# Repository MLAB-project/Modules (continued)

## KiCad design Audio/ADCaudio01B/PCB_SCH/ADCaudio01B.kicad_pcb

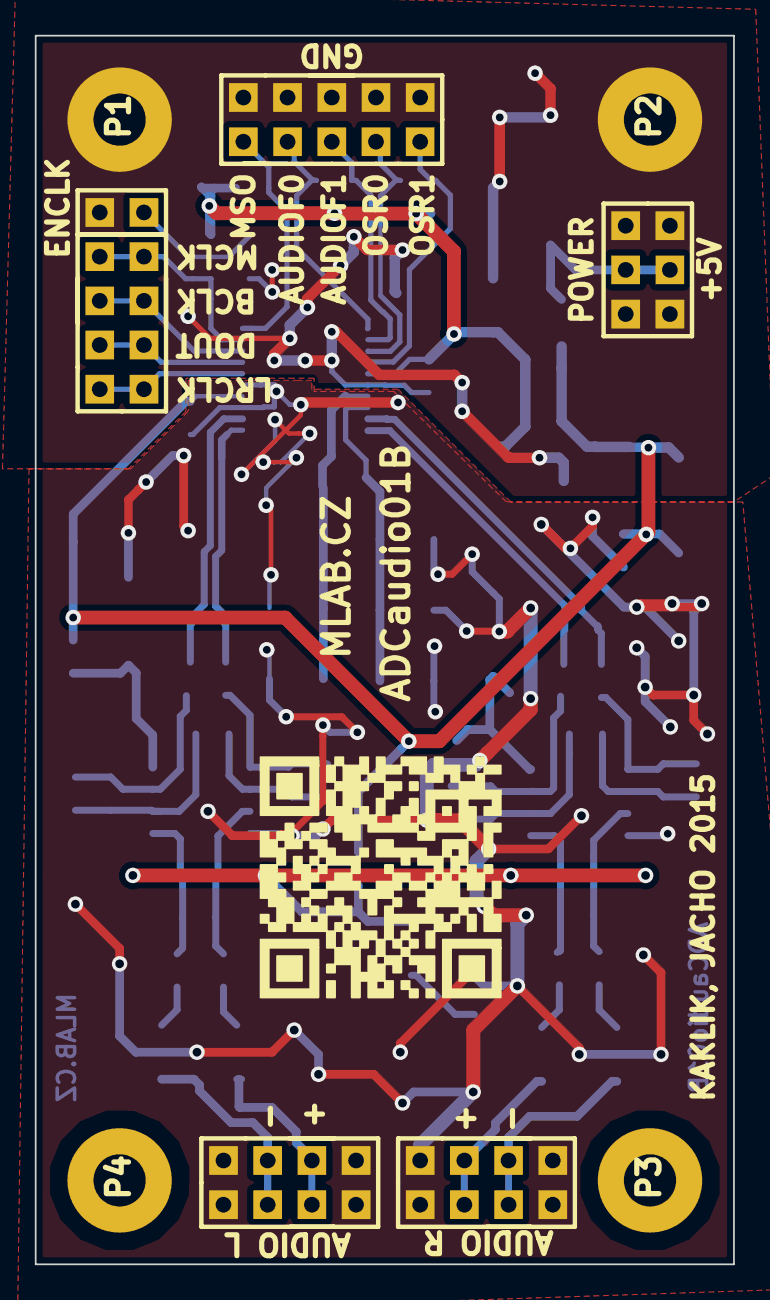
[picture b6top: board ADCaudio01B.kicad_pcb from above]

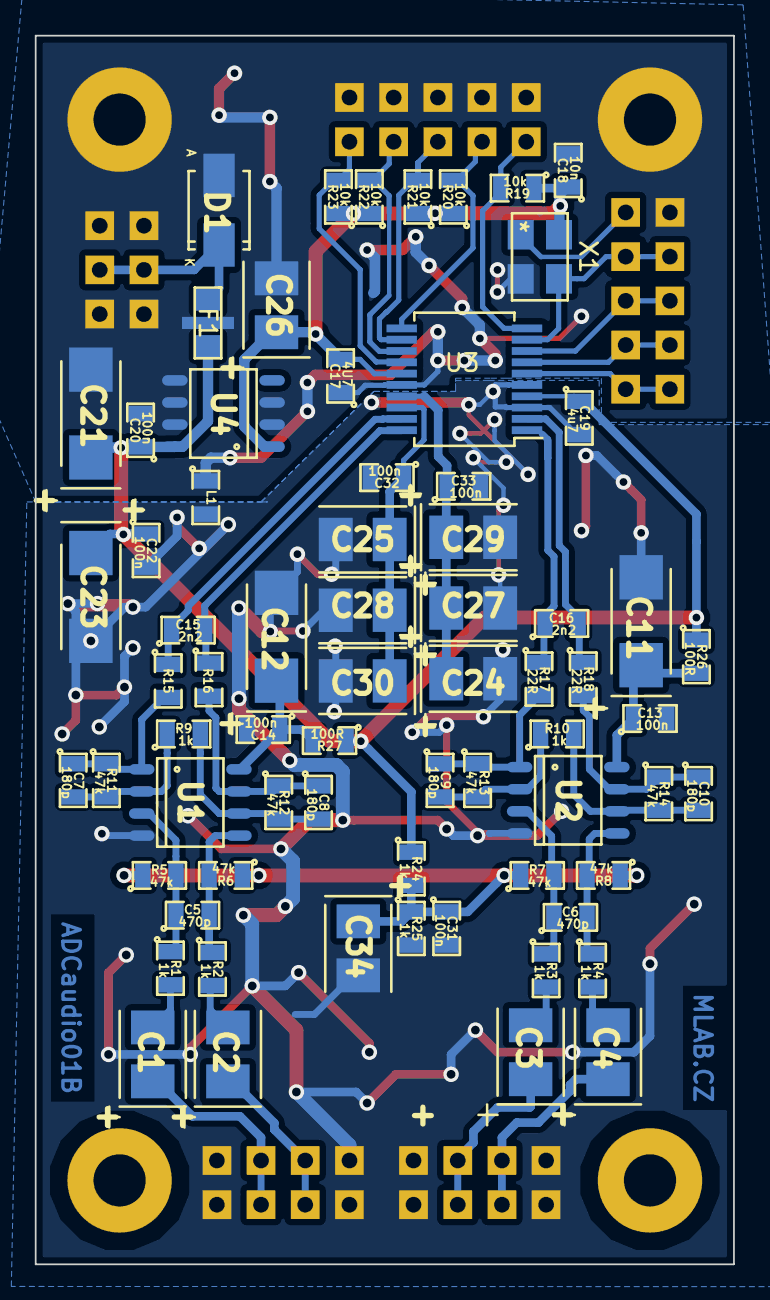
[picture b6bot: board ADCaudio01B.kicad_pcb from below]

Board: 2 copper layers, 40.1 x 70.6 mm, 79 parts (69 on the bottom side), 44 nets.

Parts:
C1, C2, C3, C4, C24, C25, C26, C27, C28, C29, C30: 10u; TantalC_SizeB_Reflow
C5, C6: 470p; SMD-0805
C7, C8, C9, C10: 180p; SMD-0805
C11, C12, C21, C23: 47u; TantalC_SizeC_Reflow
C13, C14, C20, C22, C31, C32, C33: 100n; SMD-0805
C15, C16: 2n2; SMD-0805
C17: 4U7; SMD-0805
C18: 10n; SMD-0805
C19: 4u7; SMD-0805
C34: 10uF; TantalC_SizeB_Reflow
D1: M4; Diode-SMA_Standard
F1: NFM21PC105; FIR1
J1, J2, J5: JUMP_4X2; Pin_Header_Straight_2x04
J3: JUMP_3X2; Pin_Header_Straight_2x03
J4: CONN1_2; Pin_Header_Straight_2x01
J6: JUMP2_5X2; Pin_Header_Straight_2x05
L1: BLM21PG300SN1D; SMD-0805
P1, P2, P3, P4: _; MountingHole_3mm
R1, R2, R3, R4, R9, R10, R24, R25: 1k; SMD-0805
R5, R6, R7, R8, R11, R12, R13, R14: 47k; SMD-0805
R15, R16, R17, R18: 22R; SMD-0805
R19, R20, R21, R22, R23: 10k; SMD-0805
R26, R27: 100R; SMD-0805
U1, U2: LT6231CS; SO-8
U3: WM8786; SSOP-20_5.3x7.2mm_Pitch0.65mm
U4: LE33CD; SO-8
X1: ASFL1-24.576MHZ-EK; ASFL1

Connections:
+3.3V: C17.2, C18.1, C26.1, R19.1, R20.1, R21.1, R22.1, R23.1, U3.15, U4.1, X1.4
+5V: C19.1, C20.1, C21.1, C22.1, C23.1, F1.3, R24.1, R26.1, R27.1, U3.4, U4.8
/AINL+: C16.1, R17.1, U3.1
/AINL-: C16.2, R18.1, U3.2
/AINR+: C15.2, R16.1, U3.20
/AINR-: C15.1, R15.1, U3.19
/AUDIOF0: J6.7, R20.2, U3.11
/AUDIOF1: J6.8, R21.2, U3.12
/AVDD/2: C31.1, C34.1, R5.1, R6.1, R7.1, R8.1, R24.2, R25.1
/BCLK: J5.3, J5.6, U3.8
/DOUT: J5.2, J5.7, U3.7
/LRCLK: J5.1, J5.8, U3.6
/MCLK: J5.4, J5.5, U3.9, X1.3
/MSO: J6.6, R19.2, U3.10
/OSR0: J6.9, R22.2, U3.13
/OSR1: J6.10, R23.2, U3.14
/VCC: C12.1, C14.1, R27.2, U1.8
/VCC1: C11.1, C13.1, R26.2, U2.8
/VMIO: C24.1, C27.1, C29.1, C33.1, U3.17
/VREF: C25.1, C28.1, C30.1, C32.1, U3.18
DGND: C17.1, C18.2, C20.2, C21.2, C26.2, D1.1, F1.2, J3.1, J3.3, J3.4, J3.6, J4.1, J6.1, J6.2, J6.3, J6.4, J6.5, L1.1, P1.1, P2.1, U3.16, U4.2, U4.3, U4.5, U4.6, U4.7, X1.2
GNDA: C11.2, C12.2, C13.2, C14.2, C19.2, C22.2, C23.2, C24.2, C25.2, C27.2, C28.2, C29.2, C30.2, C31.2, C32.2, C33.2, C34.2, J1.1, J1.4, J1.5, J1.8, J2.1, J2.4, J2.5, J2.8, L1.2, R25.2, U1.4, U2.4, U3.3, U3.5
unnamed: C1.1, J1.3, J1.6
unnamed: C1.2, R1.2
unnamed: C2.1, J1.2, J1.7
unnamed: C2.2, R2.2
unnamed: C3.1, J2.3, J2.6
unnamed: C3.2, R3.2
unnamed: C4.1, J2.2, J2.7
unnamed: C4.2, R4.2
unnamed: C5.1, R1.1, R5.2, U1.3
unnamed: C5.2, R2.1, R6.2, U1.5
unnamed: C6.1, R3.1, R7.2, U2.3
unnamed: C6.2, R4.1, R8.2, U2.5
unnamed: C7.1, R11.1, R15.2, U1.1
unnamed: C7.2, R9.1, R11.2, U1.2
unnamed: C8.1, R12.1, R16.2, U1.7
unnamed: C8.2, R9.2, R12.2, U1.6
unnamed: C9.1, R13.1, R17.2, U2.1
unnamed: C9.2, R10.1, R13.2, U2.2
unnamed: C10.1, R14.1, R18.2, U2.7
unnamed: C10.2, R10.2, R14.2, U2.6
unnamed: D1.2, F1.1, J3.2, J3.5
unnamed: J4.2, X1.1

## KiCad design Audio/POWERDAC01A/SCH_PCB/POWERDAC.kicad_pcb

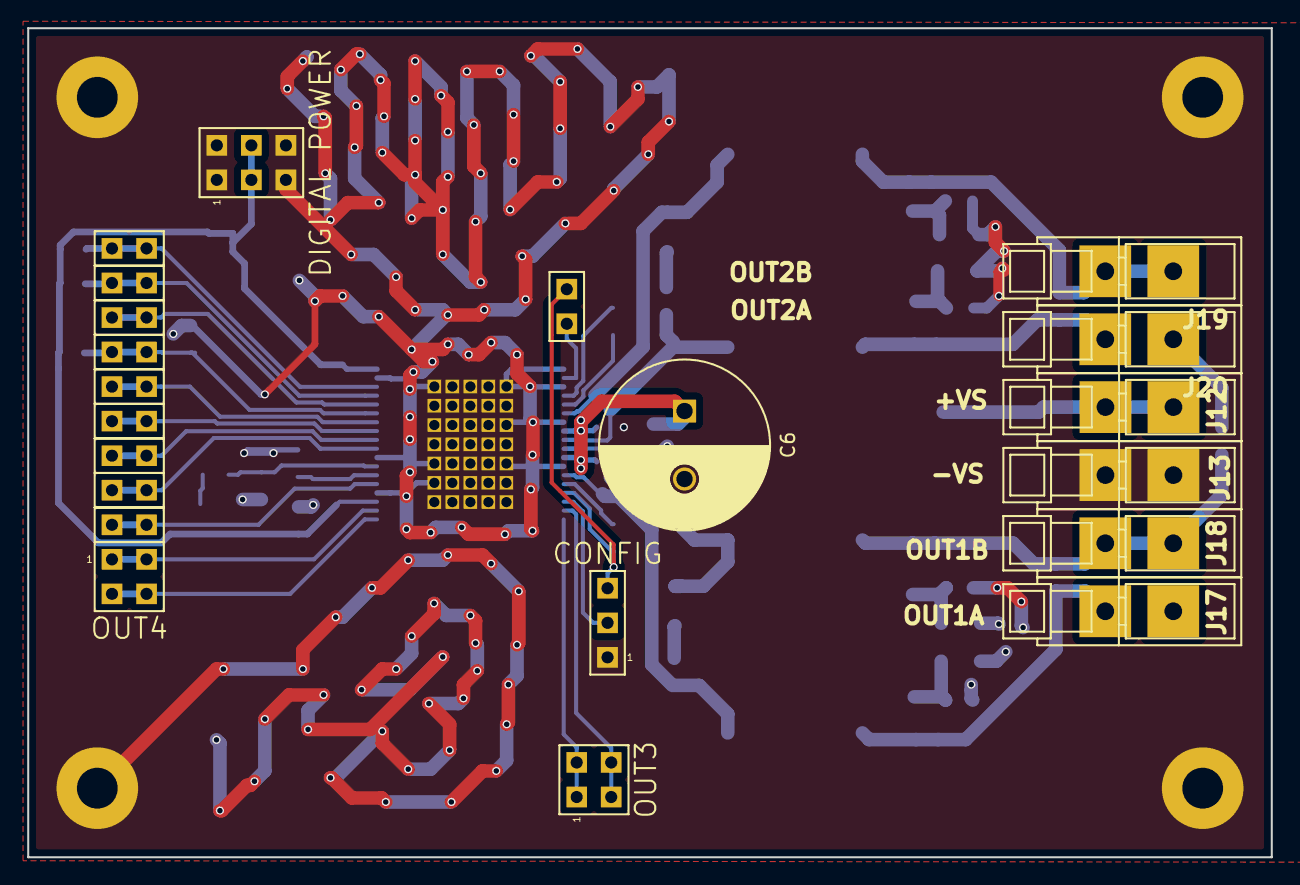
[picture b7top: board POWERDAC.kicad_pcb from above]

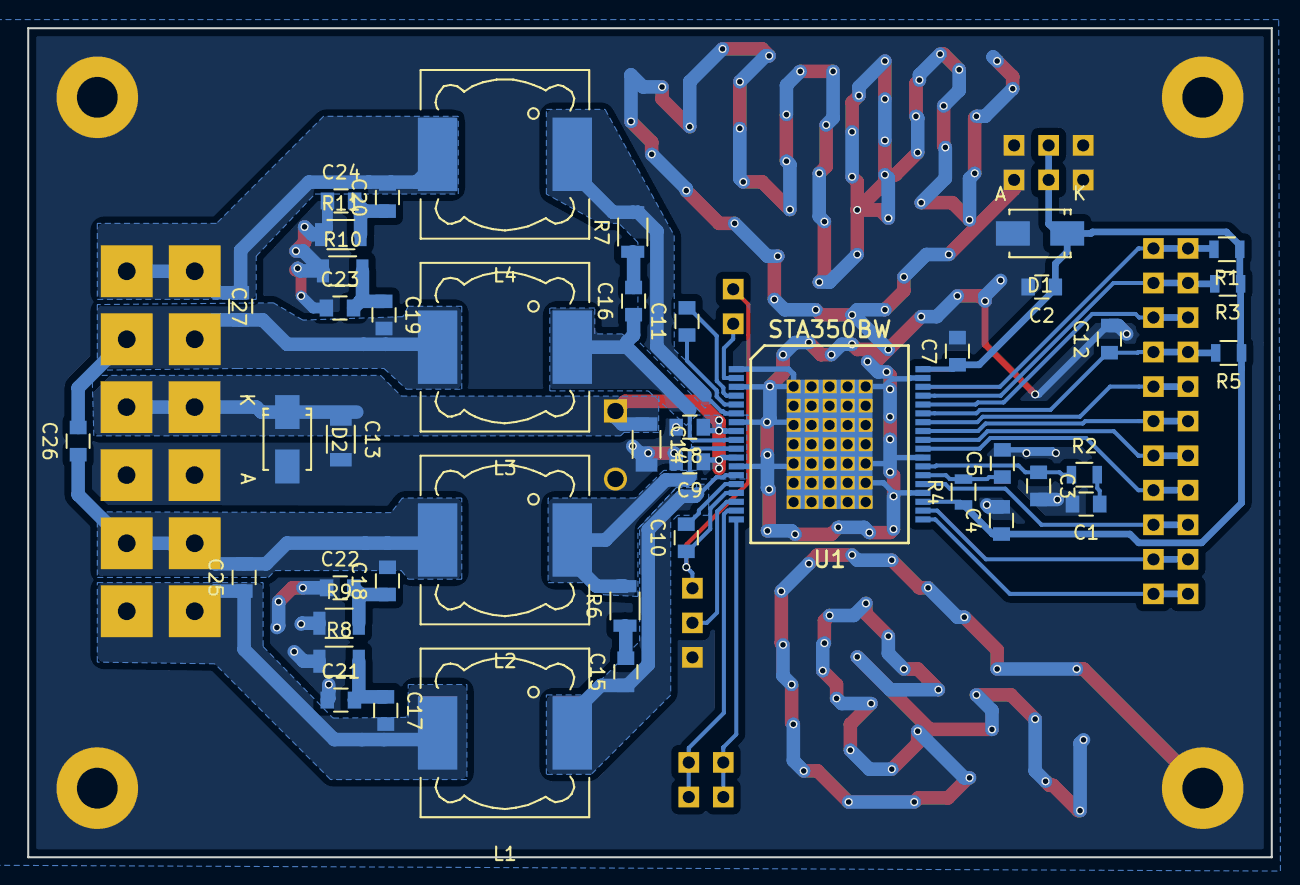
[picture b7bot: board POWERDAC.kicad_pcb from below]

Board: 2 copper layers, 91.4 x 61.0 mm, 69 parts (44 on the bottom side), 39 nets.

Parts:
C1: 4n7; C_0805
C2: 22uF/6.3V; C_0805
C3: 680p; C_0805
C4, C5, C7, C8, C9, C10, C11, C17, C18, C19, C20, C21, C22, C23, C24: 100nF; C_0805
C6: 1000uF/35V; C_Radial_D12.5_L25_P5
C12: 1nF; C_0805
C13, C14: 1uF/35V; C_1206
C15, C16: 330p; C_0805
C25, C27: 680nF; C_0805
C26: 1uF; C_0805
D1, D2: M4; SMA_Standard
J1: CONFIG; Straight_1x03
J2: DIGITAL POWER; Straight_2x03
J3: PWRDN; Straight_1x02
J4: INT_LINE; Straight_1x02
J5: SDA; Straight_1x02
J6: SCL; Straight_1x02
J7: SDI; Straight_1x02
J8: LRCKI; Straight_1x02
J9: XTI; Straight_1x02
J10: BICKI; Straight_1x02
J11: SA; Straight_1x02
J12: +VS; TerminalBlock_WAGO_256_RM5mm_1pol
J13: -VS; TerminalBlock_WAGO_256_RM5mm_1pol
J14: RESET; Straight_1x02
J15: OUT3; Straight_2x02
J16: OUT4; Straight_2x02
J17: OUT1A; TerminalBlock_WAGO_256_RM5mm_1pol
J18: OUT1B; TerminalBlock_WAGO_256_RM5mm_1pol
J19: OUT2B; TerminalBlock_WAGO_256_RM5mm_1pol
J20: OUT2A; TerminalBlock_WAGO_256_RM5mm_1pol
L1, L2, L3, L4: 15uH; Choke_SMD_12x12mm_h6mm
M1, M2, M3, M4: HOLE; MountingHole_3mm
R1, R3, R5: 10k; R_0805
R2: 2k2; R_0805
R4: 2R2; R_0805
R6, R7: 20; R_1206
R8, R9, R10, R11: 4R7; R_1206
U1: STA350BW; PowerSSO-36

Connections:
+3V3: C2.1, C4.1, C7.1, D1.1, J2.3, J2.4, R1.1, R3.1, R4.1, R5.1, U1.21, U1.36
GND: C1.2, C2.2, C3.2, C4.2, C5.2, C6.2, C7.2, C8.2, C9.2, C12.2, C13.2, C14.2, C21.1, C22.1, C23.1, C24.1, D1.2, D2.2, J1.1, J2.1, J2.2, J2.5, J2.6, J13.1, M1.1, M2.1, M3.1, M4.1, R8.1, R9.1, R10.1, R11.1, U1.1, U1.3, U1.7, U1.12, U1.22, U1.26, U1.35, U1.37
unnamed: C1.1, R2.2
unnamed: C3.1, R2.1, U1.25
unnamed: C5.1, R4.2, U1.24
unnamed: C10.2, U1.14
unnamed: C11.1, U1.5
unnamed: C11.2, U1.4
unnamed: C12.1, J14.1, J14.2, R5.2, U1.31
unnamed: C15.1, L1.1, U1.13
unnamed: C15.2, R6.1
unnamed: C16.1, L3.1, U1.9
unnamed: C16.2, R7.1
unnamed: C17.1, C21.2, R8.2
unnamed: C17.2, C25.1, J17.1, L1.2
unnamed: C18.1, C22.2, R9.2
unnamed: C18.2, C25.2, C26.1, J18.1, L2.2
unnamed: C19.1, C23.2, R10.2
unnamed: C19.2, C26.2, C27.1, J20.1, L3.2
unnamed: C20.1, C24.2, R11.2
unnamed: C20.2, C27.2, J19.1, L4.2
unnamed: J1.2, U1.16
unnamed: J3.1, J3.2, U1.23
unnamed: J4.1, J4.2, U1.32
unnamed: J5.1, J5.2, R3.2, U1.33
unnamed: J6.1, J6.2, R1.2, U1.34
unnamed: J7.1, J7.2, U1.30
unnamed: J8.1, J8.2, U1.29
unnamed: J9.1, J9.2, U1.27
unnamed: J10.1, J10.2, U1.28
unnamed: J11.2, U1.2
unnamed: J15.1, J15.2, U1.18
unnamed: J15.3, J15.4, U1.17
unnamed: J16.1, J16.2, U1.20
unnamed: J16.3, J16.4, U1.19
unnamed: L2.1, R6.2, U1.10
unnamed: L4.1, R7.2, U1.6
VCC: C6.1, C8.1, C9.1, C13.1, C14.1, D2.1, J12.1, U1.8, U1.11
VDD: C10.1, J1.3, J11.1, U1.15

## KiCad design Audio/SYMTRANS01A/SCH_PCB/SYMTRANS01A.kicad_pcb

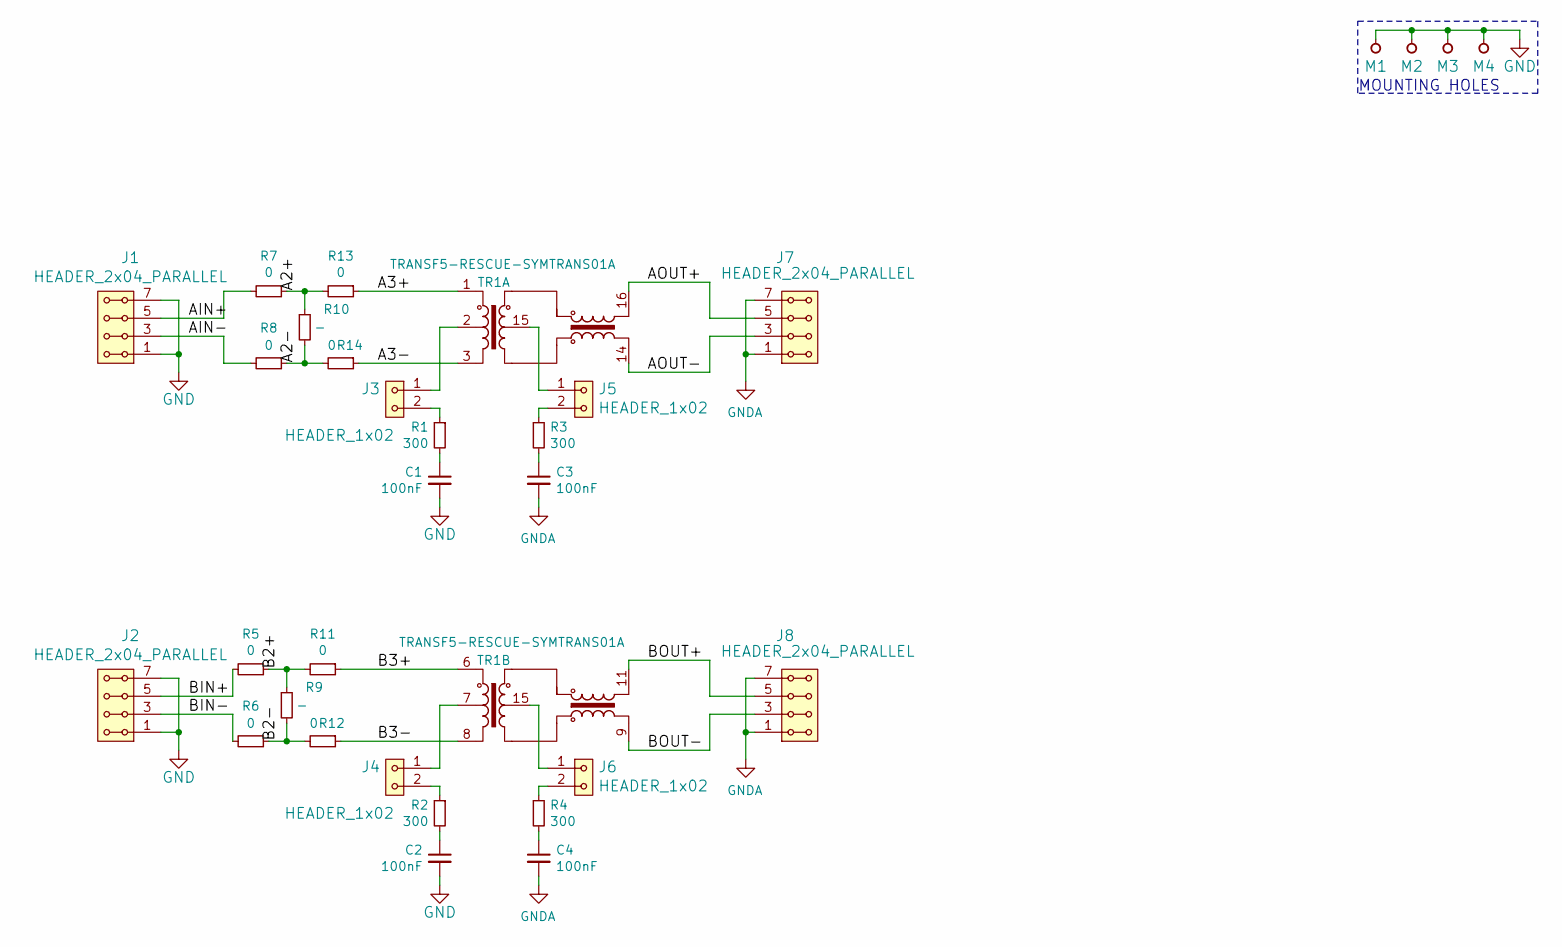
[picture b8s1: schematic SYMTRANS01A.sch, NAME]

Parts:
C1, C2, C3, C4: 100nF; SMD-0805
J1, J2, J7, J8: HEADER_2x04_PARALLEL; Straight_2x04
J3, J4, J5, J6: HEADER_1x02; Straight_2x01
M1, M2, M3, M4: HOLE; MountingHole_3mm
R1, R2, R3, R4: 300; SMD-0805
R5, R6, R7, R8, R11, R12, R13, R14: 0; SMD-0805
R9, R10: -; SMD-0805
TR1: TRANSF5-RESCUE-SYMTRANS01A; H110X_H1121_HX1188

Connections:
/A2+: R7.1, R10.1, R13.2
/A2-: R8.1, R10.2, R14.2
/A3+: R13.1, TR1.1
/A3-: R14.1, TR1.3
/AIN+: J1.5, J1.6, R7.2
/AIN-: J1.3, J1.4, R8.2
/AOUT+: J7.5, J7.6, TR1.16
/AOUT-: J7.3, J7.4, TR1.14
/B2+: R5.1, R9.1, R11.2
/B2-: R6.1, R9.2, R12.2
/B3+: R11.1, TR1.6
/B3-: R12.1, TR1.8
/BIN+: J2.5, J2.6, R5.2
/BIN-: J2.3, J2.4, R6.2
/BOUT+: J8.5, J8.6, TR1.11
/BOUT-: J8.3, J8.4, TR1.9
GND: C1.2, C2.2, J1.1, J1.2, J1.7, J1.8, J2.1, J2.2, J2.7, J2.8, M1.1, M2.1, M3.1, M4.1
GNDA: C3.2, C4.2, J7.1, J7.2, J7.7, J7.8, J8.1, J8.2, J8.7, J8.8
unnamed: C1.1, R1.2
unnamed: C2.1, R2.2
unnamed: C3.1, R3.2
unnamed: C4.1, R4.2
unnamed: J3.1, TR1.2
unnamed: J3.2, R1.1
unnamed: J4.1, TR1.7
unnamed: J4.2, R2.1
unnamed: J5.2, R3.1
unnamed: J6.2, R4.1

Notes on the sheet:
MOUNTING HOLES

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
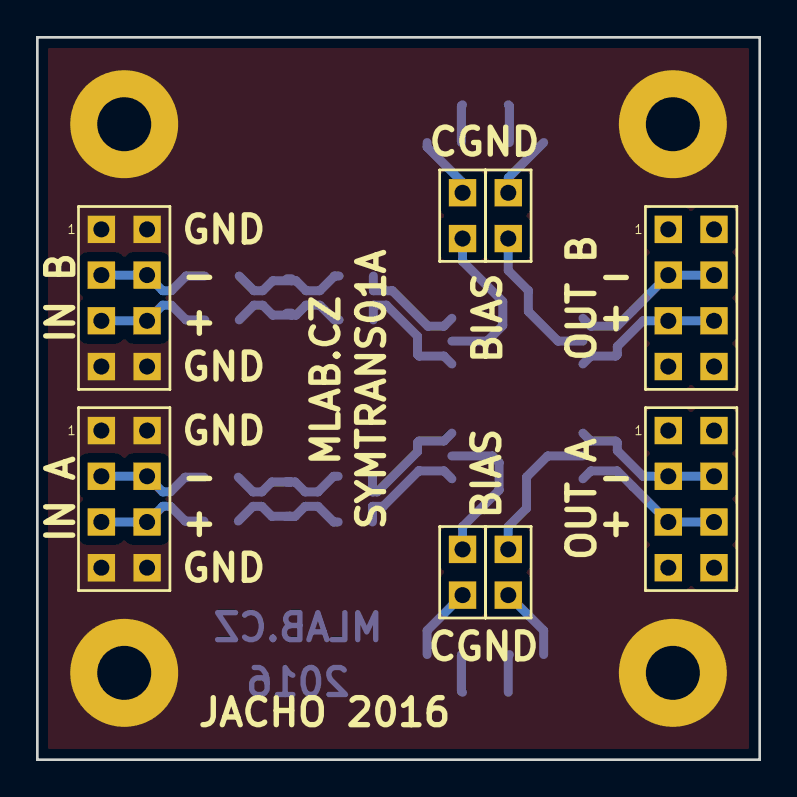
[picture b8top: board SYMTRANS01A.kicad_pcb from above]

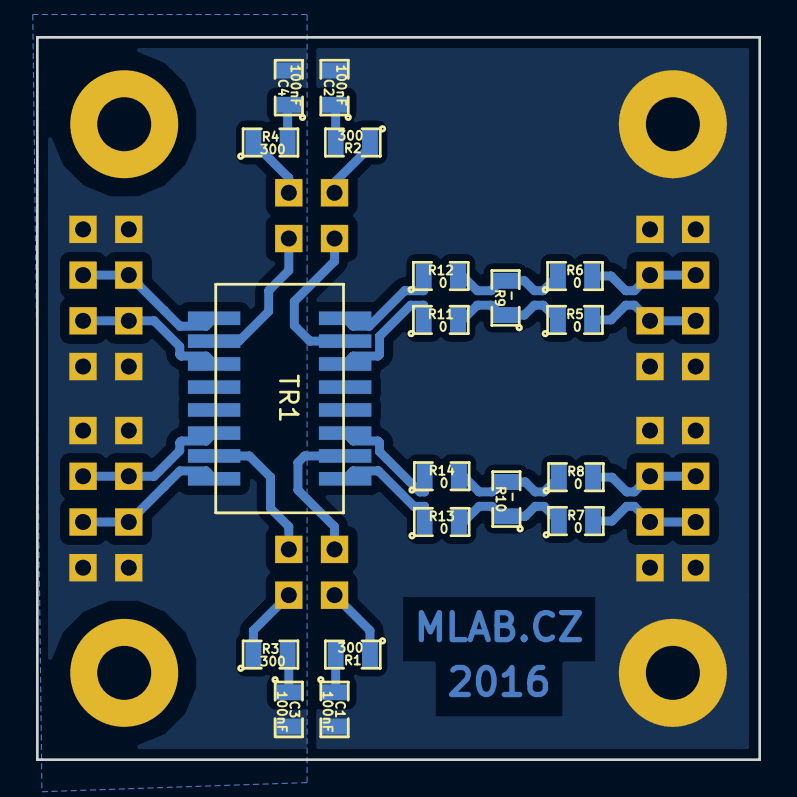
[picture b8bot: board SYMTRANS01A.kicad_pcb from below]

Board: 2 copper layers, 40.1 x 40.1 mm, 31 parts (19 on the bottom side), 30 nets.
